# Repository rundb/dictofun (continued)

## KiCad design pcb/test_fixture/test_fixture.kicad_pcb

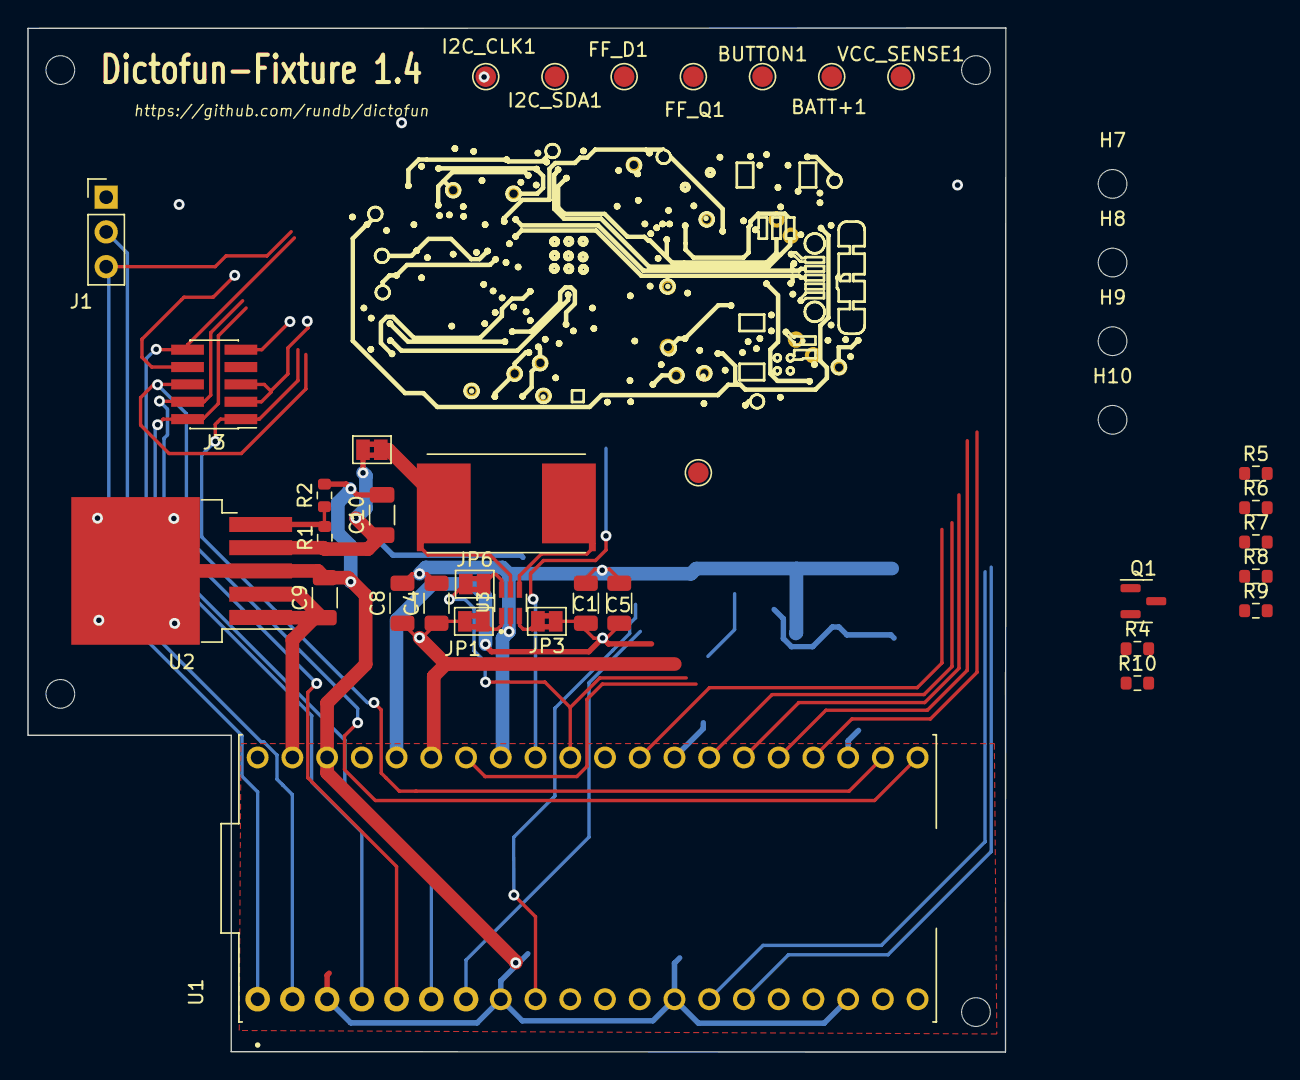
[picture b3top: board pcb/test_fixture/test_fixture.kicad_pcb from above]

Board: 2 copper layers, 71.5 x 74.9 mm, 59 parts (0 on the bottom side), 30 nets.

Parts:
BATT+1: TestPoint_Pad_D1.5mm
BUTTON1: TestPoint_Pad_D1.5mm
C1, C4: 1u; R_1206_3216Metric
C5, C8: 100n; R_1206_3216Metric
C9: 10u; R_1206_3216Metric
C10: 22u; C_1206_3216Metric
FF_CLK1: TestPoint_Pad_D1.5mm
FF_D1: TestPoint_Pad_D1.5mm
FF_Q1: TestPoint_Pad_D1.5mm
H3, H4, H5, H6: Outer PCB Mount; MountingHole_2.1mm
H7, H8, H9, H10: Stand Mount; MountingHole_2.1mm
I2C_CLK1, I2C_SDA1: TestPoint_Pad_D1.5mm
J1: UART; PinHeader_1x03_P2.54mm_Vertical
J3: Conn_ARM_JTAG_SWD_10; PinHeader_2x05_P1.27mm_Vertical_SMD
JP1, JP3, JP5, JP6: Jumper_2_Bridged; SolderJumper-2_P1.3mm_Bridged2Bar_Pad1.0x1.5mm
POGO1, POGO2, POGO3, POGO5, POGO6, POGO7, POGO8, POGO10, POGO11, POGO12, POGO13, POGO14, POGO15, POGO16, POGO19, POGO21, POGO22: pogo; POGO
Q1: NMOS; SOT-23
R1: 415; R_0603_1608Metric
R2: 187; R_0603_1608Metric
R3: 0.04; R_Shunt_Vishay_WSR2_WSR3_KelvinConnection
R4, R5, R6: 100K; R_0603_1608Metric
R7: 200K; R_0603_1608Metric
R8: 300K; R_0603_1608Metric
R9, R10: 1K; R_0603_1608Metric
U1: SC0915; MODULE_SC0915
U2: MIC29302WU; TO-263-5_TabPin3
U3: INA186A5IDCKR; SOT65P210X110-6N
VCC_SENSE1: TestPoint_Pad_D1.5mm

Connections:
+3.3V: C1.1, C5.1, JP3.1 (A), U1.36 (3V3_OUT)
+3.3VADC: C4.1, C8.1, JP1.1 (A), U1.35 (ADC_VREF)
+5V: C9.1, U1.39 (VSYS), U2.1 (EN), U2.2 (VIN)
/BATT+: BATT+1.1, POGO13.1, POGO19.1, R3.2, U3.4
/BUTTON: BUTTON1.1, POGO7.1, Q1.3 (S), R7.1
/BUTTON_CTRL: R4.1, R9.1, R10.1
/BUTTON_DIVIDED: R7.2, R8.1, U1.7 (GP5)
/CURRENT_SENSE_OUTPUT: JP6.1 (A), U1.31 (GP26)
/FF_CLK: FF_CLK1.1, POGO10.1, U1.26 (GP20)
/FF_D: FF_D1.1, POGO8.1, U1.27 (GP21)
/FF_Q: FF_Q1.1, POGO15.1, U1.29 (GP22)
/I2C_CLK: I2C_CLK1.1, POGO11.1, U1.24 (GP18)
/I2C_DATA: I2C_SDA1.1, POGO12.1, U1.25 (GP19)
/P1.9V: POGO16.1, VCC_SENSE1.1
/SENSE_VCC: R5.2, R6.1
/SWDCLK: J3.4 (SWDCLK/TCK), POGO21.1, U1.5 (GP3)
/SWDIO: J3.2 (SWDIO/TMS), POGO22.1, U1.6 (GP4)
/UART_RX: J1.3, POGO1.1, U1.1 (GP0)
/UART_TX: J1.2, POGO5.1, U1.2 (GP1)
/VTREF: J3.1 (VTref), POGO2.1, U1.22 (GP17)
GND: C9.2, C10.2, J1.1, J3.3 (GND), J3.5 (GND), POGO3.1, POGO6.1, POGO14.1, R2.2, R4.2, R6.2, R8.2, U1.3 (GND), U1.8 (GND), U1.13 (GND), U1.18 (GND), U1.23 (GND), U1.28 (GND), U1.38 (GND), U2.3 (GND)
GNDA: C1.2, C4.2, C5.2, C8.2, U1.33 (AGND), U3.2
unnamed: JP1.2 (B), U3.1
unnamed: JP3.2 (B), U3.3
unnamed: JP5.2 (B), R3.1, U3.5
unnamed: JP6.2 (B), U3.6
unnamed: Q1.2 (G), R10.2
unnamed: R9.2, U1.9 (GP6)
unnamed: R1.2, R2.1, U2.5 (ADJ)
VDD: C10.1, JP5.1 (A), Q1.1 (D), R1.1, U2.4 (VOUT)

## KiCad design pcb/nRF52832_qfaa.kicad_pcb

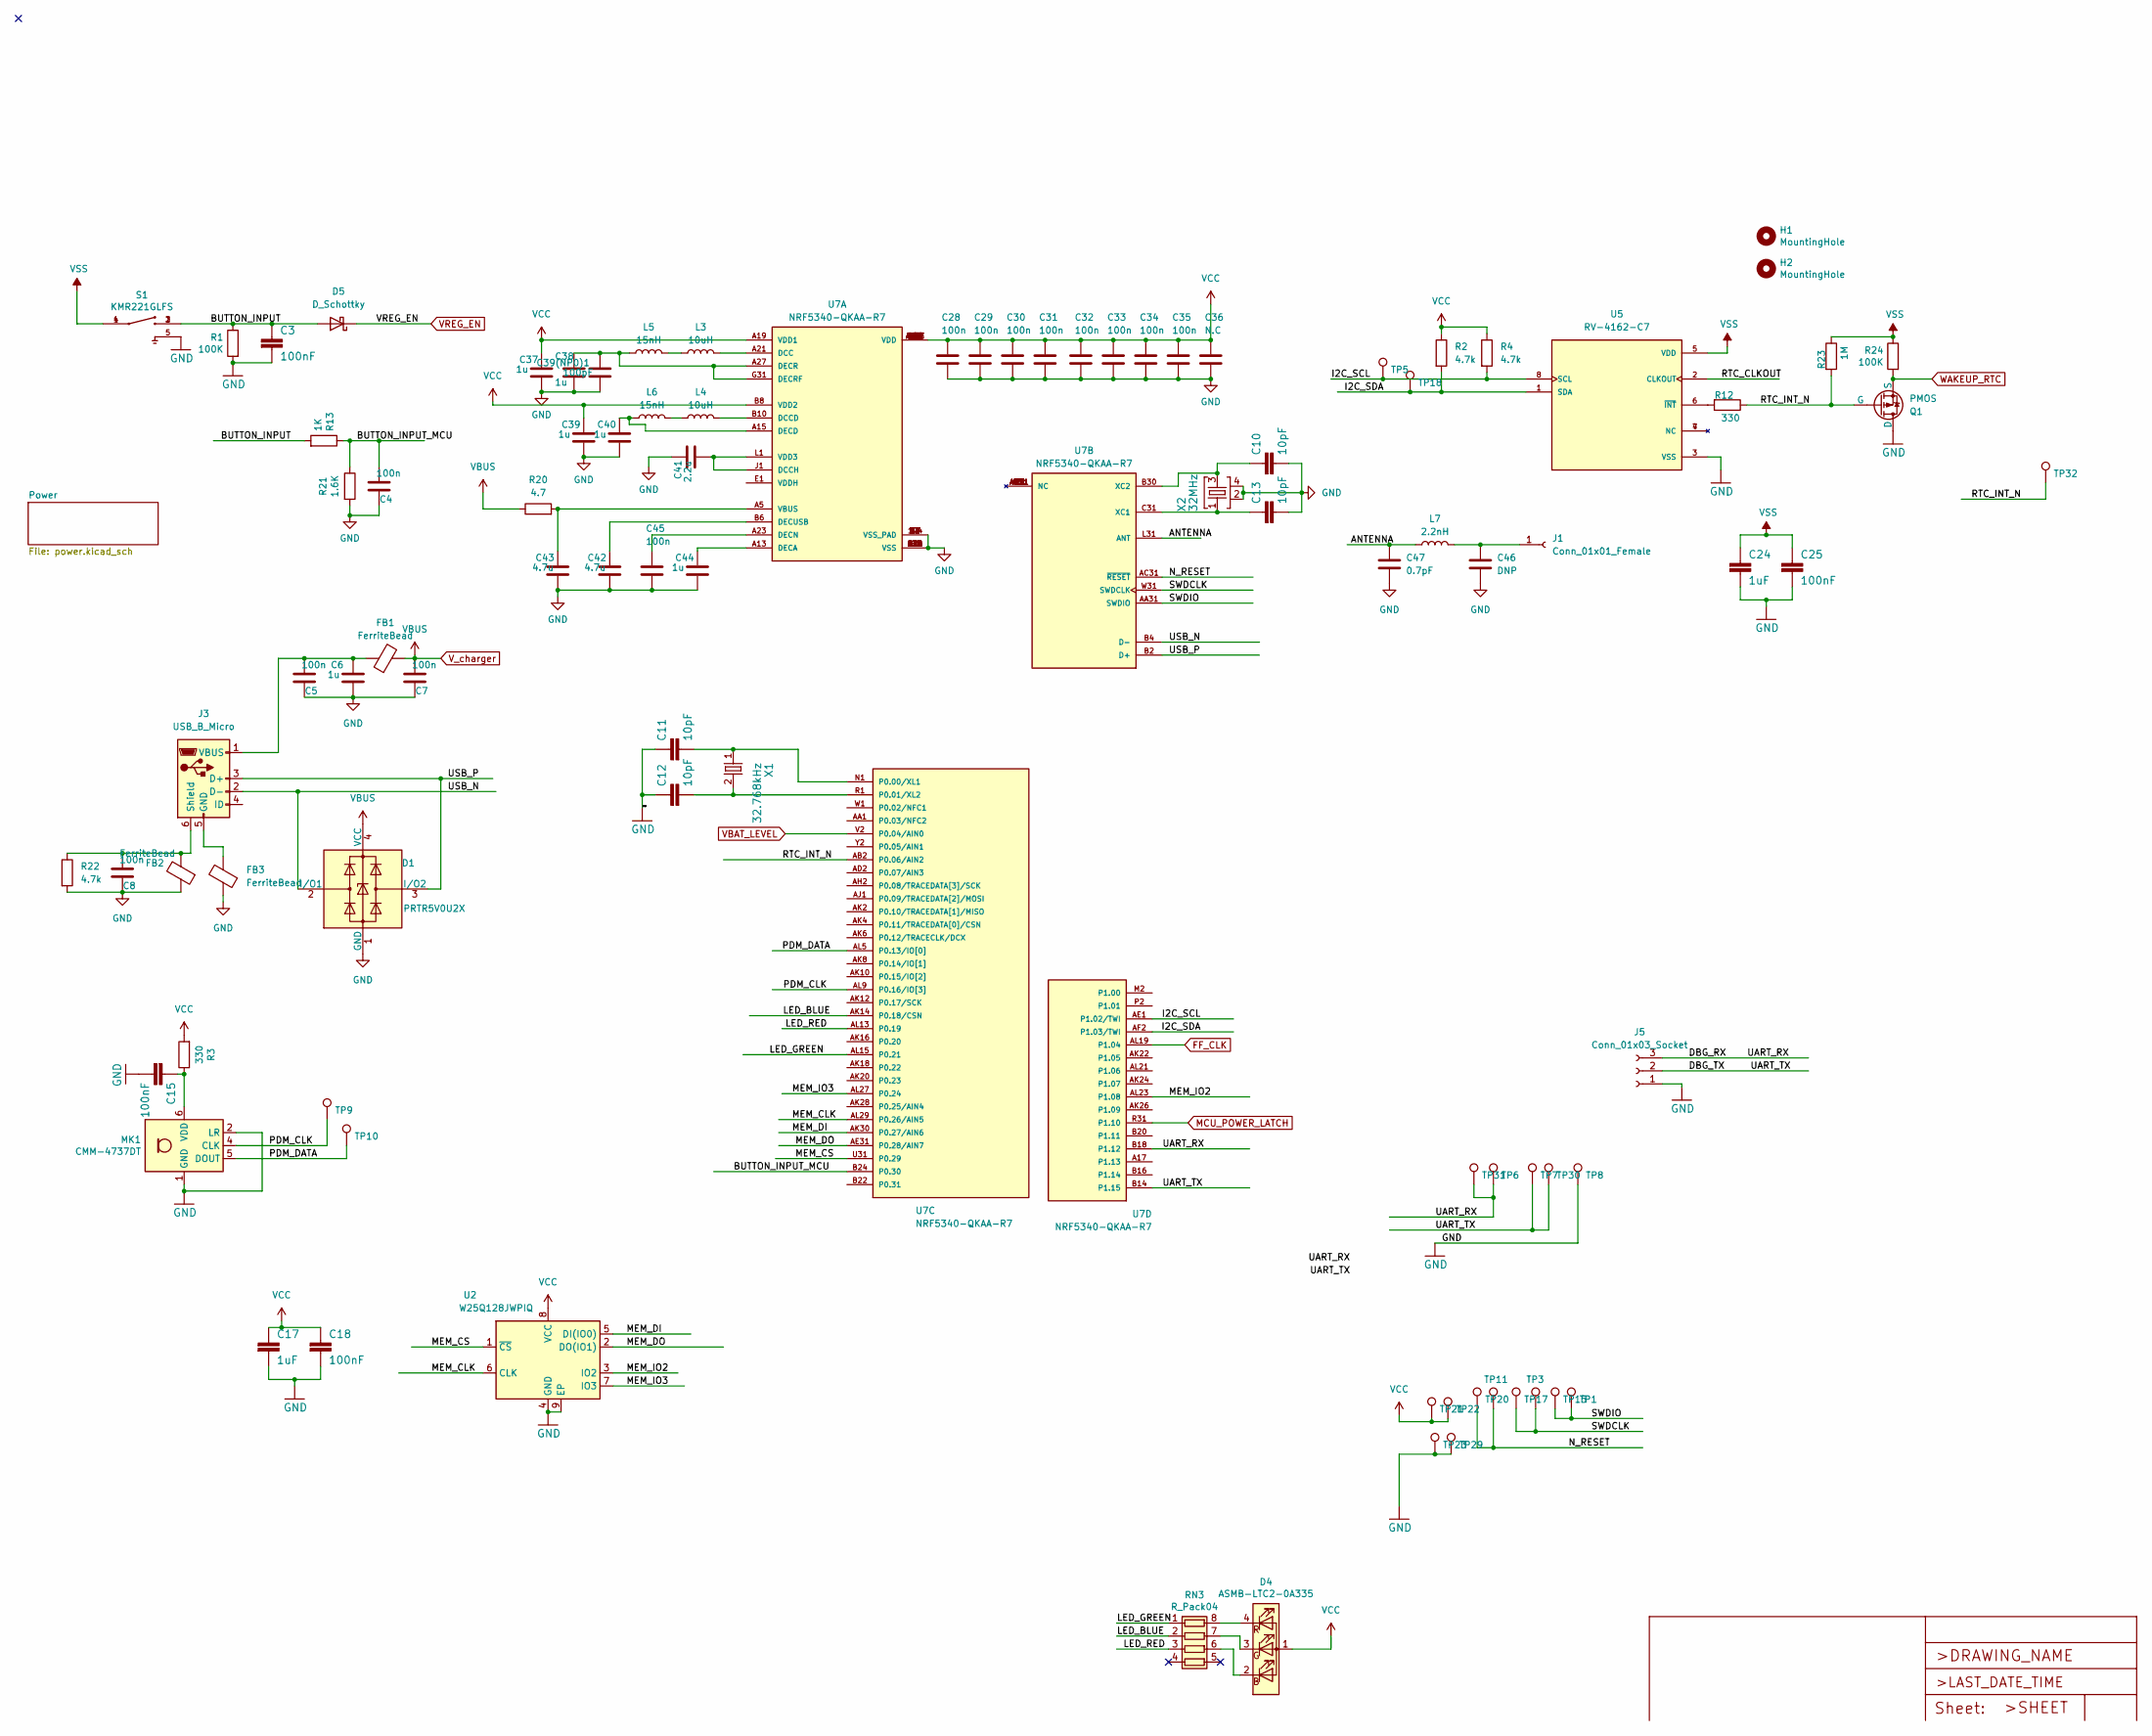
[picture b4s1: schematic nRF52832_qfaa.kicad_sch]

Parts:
C3, C15, C18, C25: 100nF; C_0402_1005Metric; LCSC C1525
C4, C5, C7, C8, C28, C29, C30, C31, C32, C33, C34, C35, C45: 100n; C_0201_0603Metric; LCSC C5142565
C6, C37, C38, C39, C40, C44: 1u; C_0402_1005Metric; LCSC C77007
C10, C13: 10pF; C_0402_1005Metric; LCSC C32949
C11, C12: 10pF; C_0201_0603Metric
C17, C24: 1uF; C_0402_1005Metric; LCSC C52923
C36: N.C; C_0201_0603Metric
C39(NP0)1: 100pF; C_0201_0603Metric
C41: 2.2u; C_0603_1608Metric; LCSC C77183
C42: 4.7u; C_0603_1608Metric; LCSC C2961288
C43: 4.7u; C_0603_1608Metric; LCSC C108342
C46: DNP; C_0201_0603Metric
C47: 0.7pF; C_0201_0603Metric
D1: PRTR5V0U2X; SOT-143; LCSC C2827688
D4: ASMB-LTC2-0A335; LED_Cree-PLCC4_2x2mm_CW
D5: D_Schottky; D_SOD-123F; LCSC C223608
FB1, FB2, FB3: FerriteBead; L_0402_1005Metric; LCSC C19136
H1, H2: MountingHole; MountingHole_1mm
J1: Conn_01x01_Female; PinHeader_1x01_P1.00mm_Vertical
J3: USB_B_Micro; USB_Micro-B_Molex-105017-0001
J5: Conn_01x03_Socket; JST_SM03B-SRSS-TB_LF__SN_
L3, L4: 10uH; L_0603_1608Metric; LCSC C5339208
L5, L6: 15nH; L_0201_0603Metric; LCSC C1332892
L7: 2.2nH; L_0201_0603Metric
MK1: CMM-4737DT; ST_HLGA-6_3.76x4.72mm_P1.65mm
Q1: PMOS; SOT-23; LCSC C332106
R1, R24: 100K; R_0402_1005Metric; LCSC C25741
R2, R4, R22: 4.7k; R_0402_1005Metric; LCSC C25900
R3, R12: 330; R_0402_1005Metric; LCSC C25104
R13: 1K; R_0402_1005Metric; LCSC C11702
R20: 4.7; R_0201_0603Metric; LCSC C166070
R21: 1.6K; R_0402_1005Metric; LCSC C25867
R23: 1M; R_0402_1005Metric; LCSC C226699
RN3: R_Pack04; R_Array_Convex_4x0402; LCSC C25726
S1: KMR221GLFS; SW_KMR221GLFS; LCSC C72443
TP1, TP3, TP5, TP6, TP7, TP8, TP9, TP10, TP11, TP15, TP17, TP18, TP20, TP21, TP22, TP23, TP29, TP30, TP31, TP32: TestPoint; TestPoint_Pad_D1.0mm
U2: W25Q128JWPIQ; WSON-8-1EP_6x5mm_P1.27mm_EP3.4x4.3mm; LCSC C2689660
U5: RV-4162-C7; IC_RV-4162-C7; PARTREV 5.1/09.2020
U7: NRF5340-QKAA-R7; XCVR_NRF5340-QKAA-R7; PARTREV 1.0
X1: 32.768kHz; Crystal_SMD_MicroCrystal_CM9V-T1A-2Pin_1.6x1.0mm
X2: 32MHz; BT-XTAL_2016_N

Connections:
/ANTENNA: C47.1, L7.1, U7.L31 (ANT)
/BUTTON_INPUT: C3.1, D5.2 (A), R1.1, R13.2, S1.2, S1.3
/BUTTON_INPUT_MCU: C4.1, R13.1, R21.1, U7.B24 (P0.30)
/DBG_RX: J5.3, TP6.1, TP31.1, U7.B18 (P1.12)
/DBG_TX: J5.2, TP7.1, TP30.1, U7.B14 (P1.15)
/I2C_SCL: R4.2, TP5.1, U5.8 (SCL), U7.AE1 (P1.02/TWI)
/I2C_SDA: R2.2, TP18.1, U5.1 (SDA), U7.AF2 (P1.03/TWI)
/LED_BLUE: RN3.2 (R2.1), U7.AK14 (P0.18/CSN)
/LED_GREEN: RN3.1 (R1.1), U7.AL15 (P0.21)
/LED_RED: RN3.3 (R3.1), U7.AL13 (P0.19)
/MEM_CLK: U2.6 (CLK), U7.AL29 (P0.26/AIN5)
/MEM_CS: U2.1 (~CS), U7.U31 (P0.29)
/MEM_DI: U2.5 (DI(IO0)), U7.AK30 (P0.27/AIN6)
/MEM_DO: U2.2 (DO(IO1)), U7.AE31 (P0.28/AIN7)
/MEM_IO2: U2.3 (IO2), U7.AL23 (P1.08)
/MEM_IO3: U2.7 (IO3), U7.AL27 (P0.24)
/N_RESET: TP11.1, TP20.1, U7.AC31 (~RESET)
/PDM_CLK: MK1.4 (CLK), TP9.1, U7.AL9 (P0.16/IO[3])
/PDM_DATA: MK1.5 (DOUT), TP10.1, U7.AL5 (P0.13/IO[0])
/RTC_CLKOUT: U5.2 (CLKOUT)
/RTC_INT_N: Q1.2 (G), R12.1, R23.2, TP32.1, U7.AB2 (P0.06/AIN2)
/SWDCLK: TP3.1, TP17.1, U7.W31 (SWDCLK)
/SWDIO: TP1.1, TP15.1, U7.AA31 (SWDIO)
/USB_N: D1.2 (I/O1), J3.2 (D-), U7.B4 (D-)
/USB_P: D1.3 (I/O2), J3.3 (D+), U7.B2 (D+)
FF_CLK: U7.AL19 (P1.04); also elsewhere on the board
GND: C3.2, C4.2, C5.2, C6.2, C7.2, C8.2, C10.2, C11.1, C12.1, C13.2, C15.2, C17.2, C18.2, C24.2, C25.2, C28.2, C29.2, C30.2, C31.2, C32.2, C33.2, C34.2, C35.2, C36.2, C37.2, C38.2, C39.2, C39(NP0)1.2, C40.2, C41.1, C42.2, C43.2, C44.2, C45.2, C46.2, C47.2, D1.1 (GND), FB2.1, FB3.1, J5.1, MK1.1 (GND), MK1.2 (LR), MK1.3 (GND), Q1.1 (D), R1.2, R21.2, R22.2, S1.5, TP8.1, TP23.1, TP29.1, U2.4 (GND), U2.9 (EP), U5.3 (VSS), U7.35 (VSS_PAD), U7.36 (VSS_PAD), U7.37 (VSS_PAD), U7.38 (VSS_PAD), U7.39 (VSS_PAD), U7.40 (VSS_PAD), U7.41 (VSS_PAD), U7.43 (VSS_PAD), U7.44 (VSS_PAD), U7.45 (VSS_PAD), U7.46 (VSS_PAD), U7.47 (VSS_PAD), U7.48 (VSS_PAD), U7.49 (VSS_PAD), U7.50 (VSS_PAD), U7.51 (VSS_PAD), U7.104 (VSS_PAD), U7.A25 (VSS), U7.B12 (VSS), U7.B26 (VSS), U7.G1 (VSS), U7.H2 (VSS), U7.J31 (VSS), X2.2, X2.4; also elsewhere on the board
MCU_POWER_LATCH: U7.R31 (P1.10); also elsewhere on the board
unnamed: D4.2 (BK), RN3.6 (R3.2)
unnamed: D4.3 (GK), RN3.7 (R2.2)
unnamed: D4.4 (RK), RN3.8 (R1.2)
unnamed: C46.1, J1.1, L7.2
unnamed: FB3.2, J3.5 (GND)
unnamed: C8.1, FB2.2, J3.6 (Shield), R22.1
unnamed: C5.1, C6.1, FB1.1, J3.1 (VBUS)
unnamed: L3.1, L5.2
unnamed: L4.1, L6.2
unnamed: C15.1, MK1.6 (VDD), R3.1
unnamed: R12.2, U5.6 (~INT)
unnamed: L3.2, U7.A21 (DCC)
unnamed: L4.2, U7.B10 (DCCD)
unnamed: C41.2, U7.J1 (DCCH), U7.L1 (VDD3)
unnamed: C44.1, U7.A13 (DECA)
unnamed: C40.1, L6.1, U7.A15 (DECD)
unnamed: C45.1, U7.A23 (DECN)
unnamed: C38.1, C39(NP0)1.1, L5.1, U7.A27 (DECR), U7.G31 (DECRF)
unnamed: C42.1, U7.B6 (DECUSB)
unnamed: C43.1, R20.2, U7.A5 (VBUS)
unnamed: C13.1, U7.C31 (XC1), X2.1
unnamed: C10.1, U7.B30 (XC2), X2.3
unnamed: C11.2, U7.N1 (P0.00/XL1), X1.1
unnamed: C12.2, U7.R1 (P0.01/XL2), X1.2
VBAT_LEVEL: U7.V2 (P0.04/AIN0); also elsewhere on the board
VCC: C17.1, C18.1, C28.1, C29.1, C30.1, C31.1, C32.1, C33.1, C34.1, C35.1, C36.1, C37.1, C39.1, D4.1 (A), R2.1, R3.2, R4.1, TP21.1, TP22.1, U2.8 (VCC), U7.A19 (VDD1), U7.AC1 (VDD), U7.AG1 (VDD), U7.AJ31 (VDD), U7.AL3 (VDD), U7.AL7 (VDD), U7.AL11 (VDD), U7.AL17 (VDD), U7.AL25 (VDD), U7.B8 (VDD2), U7.B28 (VDD), U7.C1 (VDD), U7.E31 (VDD), U7.N31 (VDD), U7.U1 (VDD); also elsewhere on the board
VREG_EN: D5.1 (K), Q1.3 (S), R24.2; also elsewhere on the board
VSS: C24.1, C25.1, R23.1, R24.1, S1.1, S1.4, U5.5 (VDD); also elsewhere on the board
V_charger: C7.1, D1.4 (VCC), FB1.2, R20.1; also elsewhere on the board

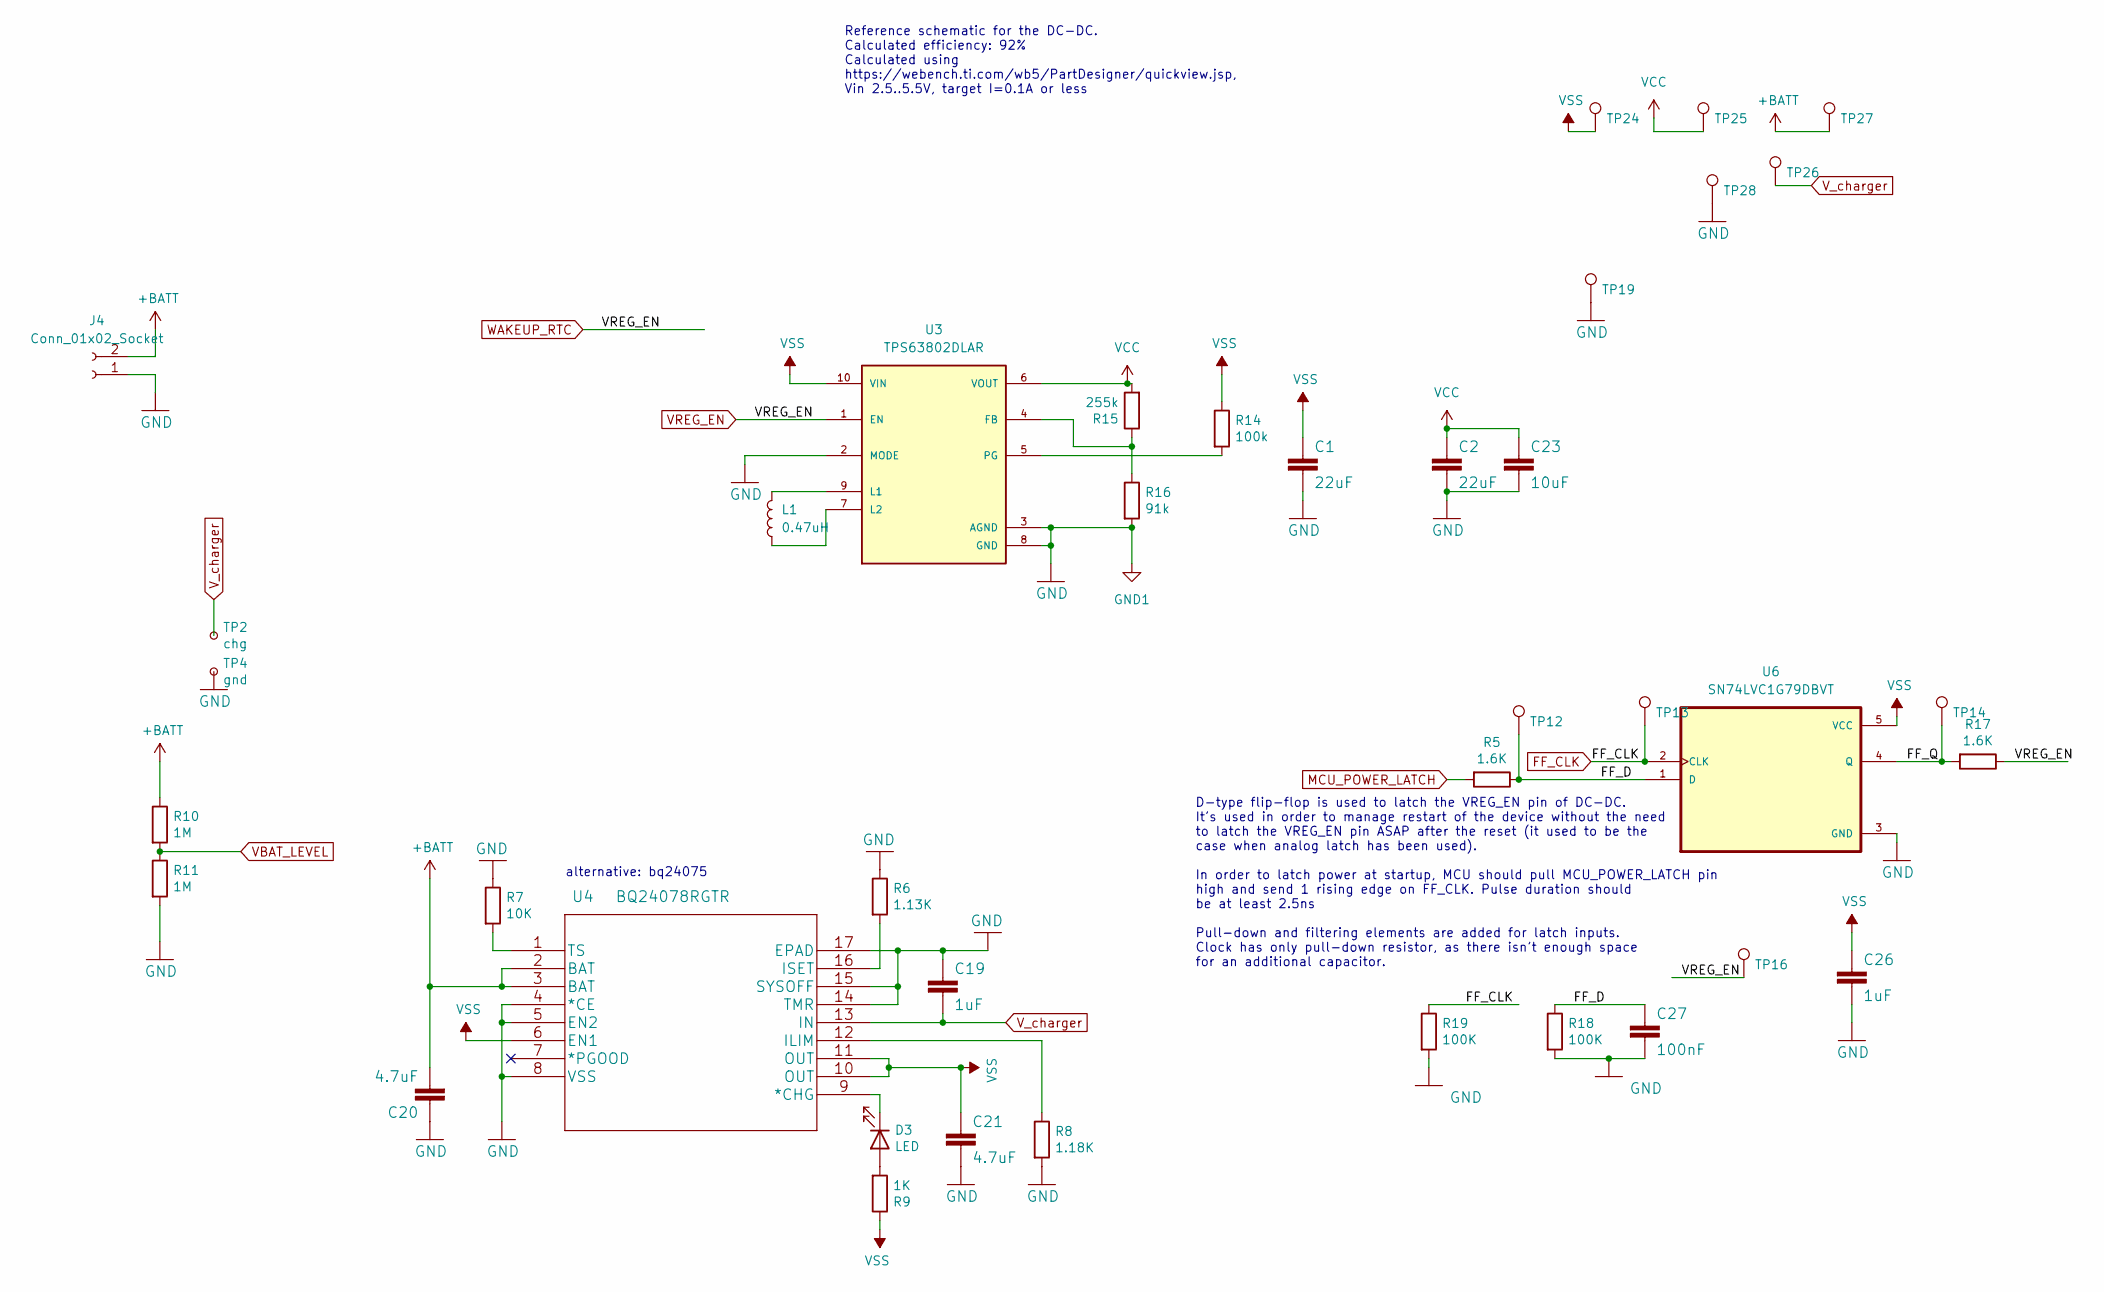
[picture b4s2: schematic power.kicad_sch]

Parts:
C1, C2: 22uF; C_0603_1608Metric; LCSC C109447
C19, C26: 1uF; C_0402_1005Metric; LCSC C52923
C20, C21: 4.7uF; C_0402_1005Metric; LCSC C23733
C23: 10uF; C_0402_1005Metric; LCSC C15525
C27: 100nF; C_0402_1005Metric; LCSC C1525
D3: LED; LED_0603_1608Metric; LCSC C131282
J4: Conn_01x02_Socket; SM02B-SRSS-TB_LF__SN_
L1: 0.47uH; L_1008_2520Metric; PartN LQM2HPNR47MG0L; LCSC C1333867
R5, R17: 1.6K; R_0402_1005Metric; LCSC C25867
R6: 1.13K; R_0402_1005Metric; LCSC C67014
R7: 10K; R_0402_1005Metric; LCSC C25744
R8: 1.18K; R_0402_1005Metric; LCSC C270651
R9: 1K; R_0402_1005Metric; LCSC C11702
R10, R11: 1M; R_0402_1005Metric; LCSC C226699
R14: 100k; R_0402_1005Metric; LCSC C25741
R15: 255k; R_0603_1608Metric; LCSC C728604
R16: 91k; R_0603_1608Metric; LCSC C227535
R18, R19: 100K; R_0402_1005Metric; LCSC C25741
TP2: chg; TestPoint_Pad_D1.0mm
TP4: gnd; TestPoint_Pad_D1.0mm
TP12, TP13, TP14, TP16, TP19, TP24, TP25, TP26, TP27, TP28: TestPoint; TestPoint_Pad_D1.0mm
U3: TPS63802DLAR; VREG_TPS63802DLAR; PARTREV B; LCSC C2845237
U4: BQ24078RGTR; VQFN-16-1EP_3x3mm_P0.5mm_EP1.45x1.45mm_ThermalVias; LCSC C15464
U6: SN74LVC1G79DBVT; SOT-23-5; LCSC C42878

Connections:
+BATT: C20.2, J4.2, R10.1, TP27.1, U4.2 (BAT), U4.3 (BAT)
/Power/FF_D: C27.1, R5.1, R18.1, TP12.1, U6.1 (D)
/Power/FF_Q: R17.2, TP14.1, U6.4 (Q)
FF_CLK: R19.1, TP13.1, U6.2 (CLK); also elsewhere on the board
GND: C1.2, C2.2, C19.1, C20.1, C21.2, C23.2, C26.2, C27.2, J4.1, R6.1, R7.1, R8.2, R11.2, R16.2, R18.2, R19.2, TP4.1, TP19.1, TP28.1, U3.2 (MODE), U3.3 (AGND), U3.8 (GND), U4.4 (*CE), U4.5 (EN2), U4.8 (VSS), U4.14 (TMR), U4.15 (SYSOFF), U4.17 (EPAD), U6.3 (GND); also elsewhere on the board
MCU_POWER_LATCH: R5.2; also elsewhere on the board
unnamed: D3.2 (A), R9.2
unnamed: D3.1 (K), U4.9 (*CHG)
unnamed: R15.1, R16.1, U3.4 (FB)
unnamed: L1.2, U3.9 (L1)
unnamed: L1.1, U3.7 (L2)
unnamed: R14.2, U3.5 (PG)
unnamed: R8.1, U4.12 (ILIM)
unnamed: R6.2, U4.16 (ISET)
unnamed: R7.2, U4.1 (TS)
VBAT_LEVEL: R10.2, R11.1; also elsewhere on the board
VCC: C2.1, C23.1, R15.2, TP25.1, U3.6 (VOUT); also elsewhere on the board
VREG_EN: R17.1, TP16.1, U3.1 (EN); also elsewhere on the board
VSS: C1.1, C21.1, C26.1, R9.1, R14.1, TP24.1, U3.10 (VIN), U4.6 (EN1), U4.10 (OUT), U4.11 (OUT), U6.5 (VCC); also elsewhere on the board
V_charger: C19.2, TP2.1, TP26.1, U4.13 (IN); also elsewhere on the board

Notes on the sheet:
alternative: bq24075
D-type flip-flop is used to latch the VREG_EN pin of DC-DC. It's used in order to manage restart of the device without the need to latch the VREG_EN pin ASAP after the reset (it used to be the case when analog latch has been used). In order to latch power at startup, MCU should pull MCU_POWER_LATCH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
Reference schematic for the DC-DC. Calculated efficiency: 92% Calculated using https://webench.ti.com/wb5/PartDesigner/quickview.jsp, Vin 2.5..5.5V, target I=0.1A or less

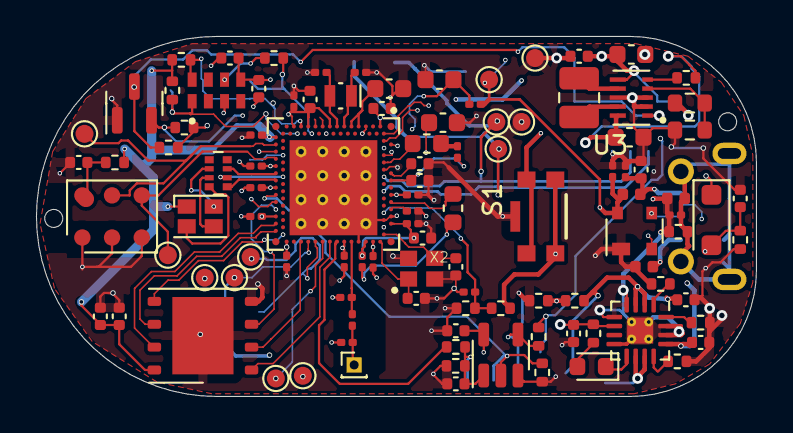
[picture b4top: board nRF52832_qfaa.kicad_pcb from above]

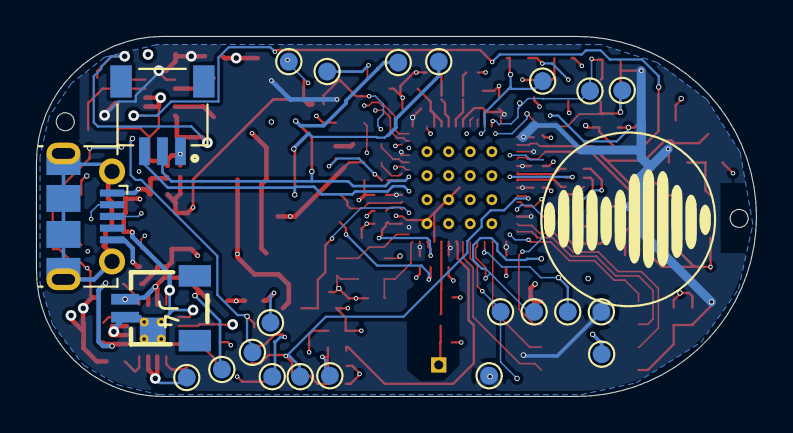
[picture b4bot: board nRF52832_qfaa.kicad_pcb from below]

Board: 4 copper layers, 40.0 x 20.0 mm, 131 parts (23 on the bottom side), 68 nets.

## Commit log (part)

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2023-01-07 implemented a primitive raw audio data sink
2023-01-08 fixes upon review
2023-01-08 [nordic] implement PDM microphone (#77)
    - implementation of PDM microphone using Nordic PDM driver
    - implementation of a data sync (targeting at integration tests)
2023-01-08 added littlefs as a third party submodule
2023-01-08 lfs: added basis for lfs sim api
2023-01-08 got rid of std::cout usage
2023-01-08 added checks of FS behavior into the test
2023-01-09 fixed target compilation error
2023-01-09 saving a compiling state of target build
2023-01-09 added memtest cli command
2023-01-09 cli infra is ready. time for the tests
2023-01-09 added memtest 2 + fixed bug in SPI flash driver implementation
2023-01-09 added submodule checkout step
2023-01-09 another attempt to fix actions
2023-01-09 fixed UT compilation issue due to different G++ versions
2023-01-10 [fw] introduce storage infrastructure (#78)
    - integrate LittleFS
    - change Spi Flash driver to use abstract interface (also implementing a setup for unit tests)
    - change SPI Flash to use synchronous access API
    - fix bug in SPI Flash driver (erase command has never been launched due to a wrong opcode)
    - implement all tasks- and cli- infrastructure for storage subsystem
2023-01-10 cleanup tasks dependencies
2023-01-10 start adding ble elements
2023-01-11 added all minimally necessary functions for BLE launch, debugging now
2023-01-11 few line ending corrections + some error handling for ble
2023-01-12 added LED control
2023-01-12 few more fixes
2023-01-12 [bugfix] fix SPI driver issue with the stack
2023-01-12 [nordic] uncomment test
2023-01-13 [test] added tests launcher for manual testing
2023-01-16 [test] adding test infrastructure for integration level tests
2023-01-23 kick off development of fts with newer requirements
2023-01-31 [ble] added control point actions, tested using nrfconnect
2023-02-01 managed to launch file list notification update
2023-02-02 implemented few corrections
2023-02-02 [ble fts] implemented file info sending
2023-02-03 fixed error with json + runtime error with unimplemented opener and getter
2023-02-03 finalized FTS data transfer function
2023-02-03 [ble fts] implement FTS data transfer (#86)
2023-02-03 added and tested FS status char behavior
2023-02-03 [ble fts] add FS status char (#87)
    * provide description in the specification
    * add implementation of FS status char and related infrastructure
    * add test in python for this characteristics check
2023-02-03 fix one test
2023-02-04 [test] refactor BLE tests subsystem to a reliable connection behavior
2023-02-04 added relevant methods to FTS python module, few more needed
2023-02-06 added tests of file info getter
2023-02-06 finalized tests for BLE FTS
2023-02-06 extended comments
2023-02-06 [test fts] refactoring BLE FTS infrasturcture (#89)
    * separated dictofun BLE control and FTS Client code
    * improve robustness of connection to the Dictofun
    * made test output less mouthful in case of correct execution of tests
2023-02-07 continue adding fs access boilerplate
2023-02-08 successfully established communication between BLE and mem
2023-02-08 fixed issue with lfs write operations
2023-02-09 cleaned up the tests and comments before pushing
2023-02-09 few cleanups + extend tasks readme with PNG drawing
2023-02-09 [fts] connect to fts
2023-02-09 [fts] connect get_file_info to fts (#91)
2023-02-10 file data transfer works, but tests fail to run simultaneously
2023-02-10 fix commented code in fts.py
2023-02-11 [fts] integrate fs stat to littlefs
2023-02-11 [nordic] refactor: move memtests to a separate entity
2023-02-14 managed to store multiple files with mocked data in the fs
2023-02-14 managed to store records
2023-02-15 [nordic] implement records storage (#96)
    * managed to store records
    * managed to download record to PC
2023-02-19 managed to stop losing data during the write process of the record
2023-02-19 fix review findings
2023-02-19 [nordic] introduce decimation + fix LittleFS losing data issues (#97)
2023-02-19 fix tests as well
2023-02-20 [audio] fix audio quality issue
2023-02-25 added an ADPCM decoder from nordic
2023-02-25 removed unneded comments and a dummy file
2023-02-25 [codec] introduce and implement ADPCM codec (#100)
    * introduce codec itself and basic testing infra for that
    * added header to record generation (now file type and parameters are contained inside the file)
    * added download throughput measurement on the python receiver side
2023-02-26 [nordic] fixed audio glitches issue
2023-02-26 [nordic] implemented shutdown
2023-03-11 [rtc] added boilerplate for RTC
2023-03-12 [rtc] found correct config for TWI enablement
2023-03-12 [rtc] implemented i2c scan and fixed all hw/config issues
2023-03-12 [rtc] add functional I2C driver base (#112)
2023-03-13 fixed issue with values readout, timing value now is being received correctly
2023-03-13 fixed space in the end of the file
2023-03-13 use RTC output to generate file name
2023-03-14 [button] added task_button
2023-03-17 [nvm] added non-volatile storage config support
2023-03-17 [nvm] added non-volatile storage config support (#116)
2023-03-17 [ci] assuring sequential execution of jobs
2023-03-18 fixed error check result error
2023-03-18 [state] refactor task state: move cli logic out of main body
2023-03-18 [state] refactor task_state (#119)
    * [state] refactor task state: move cli logic out of main body
    * [state] move power control to separate compilation unit
2023-03-18 [state] implemented record upon button press
2023-03-18 [state] implement memory ownership switch in field modes
2023-03-19 [app] introduced shutdown upon timeout in application modes
2023-03-19 [app] implemented filesystem access keepalive for power management
2023-03-19 [led] start adding boilerplate for led implementation
2023-03-19 [led] implemented LED control
2023-03-19 [led] implement LED control (#124)
    * implemented LED control
    * implemented CLI commands for testing
2023-03-19 [led] implemented application indication (#125)
2023-03-26 [ble] implement pairing and unpairing
2023-03-30 [nordic] create patch to increase SDH task stack
2023-04-25 [ci] add setup script for rpi ci (#129)
2023-04-25 [ci] add artefacts storage job (#130)
2023-04-26 [ci] split ut and target builds by directories (#131)
2023-04-27 [ci] adding download artefact action
2023-04-27 [ci] add artefacts upload/download (#132)
2023-04-27 [ci] added actual flashing of application hex (#133)
2023-05-02 [case] added models for harness v1.3
2023-06-22 fixed reset script and added env variable to ease installation script
2023-06-22 attempt to fix paths issue
2023-06-22 [doc, ci] add harness bringup documentation + fix CI (#134)
    * [harness] added instructions on building FW for the harness
    * fix CI cmake interpreter issue
2023-07-19 [ble] made write chars notifiable (#135)
2023-07-24 remove unnecessary comma change
2023-07-25 added get_next_file_list char and surrounding boilerplate
2023-08-01 fixes upon review, comments
2023-08-05 replaced some log from info to debug level
2023-08-05 started adding version generation and printout
2023-08-05 fixed paths, now version is printed out every startup
2023-08-06 removed space
2023-08-23 introduce reasonable value limitations for time elements (until proper timing logic is implemented)
2023-08-24 ble start stop seems to be working now
2023-08-24 remove irrelevant comments
2023-08-24 [ble] add BLE stop functionality (#142)
2023-08-24 [ble] added gap param update upon connection parameter change by the peer (#143)
2023-08-26 [cts] implementing OS boilerplate for date-time setup
2023-08-26 [ble cts] add BLE CTS support (#144)
2023-08-28 changed file id type and fixed all compilation issues
2023-08-28 extend several timeouts, due to inefficiency of LFS
2023-08-28 [app] reduced timeouts before the shutdown
2023-09-25 added workaround and a warning regarding the new FS issue (missing end of the files) (#149)
2023-10-02 fix nrf sdk patch for correct building
2023-10-07 [batt] implement battery measurement task
2023-10-07 drop CI back to self-hosting
2023-10-08 apply patches in the Docker CI image
2023-10-15 [batt] added periodic battery level print to console
2023-10-15 [batt] added periodic battery level print to console (#153)
2023-10-15 added RAII time profiling printout for memory operations
2023-10-15 added RAII time profiling printout for memory operations (#155)
2023-10-15 add BLE-enabling in case of FS error prior to reset
2023-10-15 added FS formatting if memory is full/files count is too high
2023-10-15 changed battery levels, added no-op reaction in case of a low battery
2023-10-16 changed battery levels, added no-op reaction in case of a low battery (#159)
    * changed battery levels, added no-op reaction in case of a low battery
2023-10-18 [ble] removed LBS service, might affect the background discovery on iOS (#160)
2023-11-01 added memory dump command into CLI
2023-11-01 getting started with new FS
2023-11-01 started implementation of myfs mount, need to perform first file write to test
2023-11-02 managed to program descriptor correctly
2023-11-04 managed to mount, create and close files properly
2023-11-04 added test with writing 2 files
2023-11-04 start replacing lfs with myfs in integration
2023-11-05 integrated data write, time to test the audio write scenarios
2023-11-05 integrated get_file_info
2023-11-05 added file data getter integration
2023-11-05 received the first file on the ios side
2023-11-05 fixed issue with fs stat call
2023-11-05 get rid of littlefs presence
2023-11-05 tidied the myfs_access api
2023-11-05 added restart, if 0-size FTS transaction was continuously repeated
2023-11-05 removed leftover buffer allocations after LFS
2023-11-05 fixed issues
2023-11-13 reduced battery measurements frequency, added printout in case of multiple FTS commands
2023-11-20 remove stack increase
2023-11-20 added erasure of flash memory at the formatting stage (#166)
2023-11-26 measures added to assure that timeouts don't interrupt the memory erasure (#167)
2023-11-26 fixed multiple issues (#168)
    - BLE timeouts upon double recording
    - file not found reporting
    - file system repair, if not closed file was found
2023-12-03 enabled watchdog (#169)
2023-12-03 regenerated public key, changed board to DF1.3
2023-12-03 enabling DFU support in main
2023-12-03 fixed issue with btld hanging in nrf_log_flusj
2023-12-03 reenabled watchdog, cleaned up documentation
2023-12-03 corrected patch line endings
2023-12-03 (hopefully) fixed line endings
2023-12-03 Activate Bootloader and DFU (#170)
2023-12-31 fixed myfs repair infinite loop issue
2024-01-13 added additional check of button state before creating a record (#171)
2024-01-13 implemented unpairing (should be moved to device information service) (#172)
2024-01-16 assured correctness of written values
2024-01-18 added edge case of a single file
2024-01-19 wiped nrf_log mentions from myfs implementation
2024-01-19 fixed bug during fs stats call
2024-02-03 added correct closure of file in out of memory case
2024-02-09 added state transitions
2024-02-09 added polling comms between state and button tasks
2024-02-10 implemented basic out-of-memory and memory corruption use-cases
2024-02-10 added timeout processing into the main execution line, timeouts need to be adjusted
2024-02-10 a few changes on handling out of memory state
2024-02-10 moved LED control to BLE as well; fixed timeouts' issue
2024-02-11 [ci] attempt to fix self-hosted runner build folder rights issue
2024-02-17 saving the changes
2024-02-23 finalizing 1.4, going for the dry run
2024-02-23 Design Freeze DF 1.4
2024-02-23 prepared the df1.4 fabrication outputs
2024-03-13 df 1.4.52840 ready for production
2024-03-24 refactoring: collect library components at one spot, separate 1.4.52840 into a separate folder
2024-03-30 v1.4.52840 harness done
2024-03-30 applied changes after placing engineering files for fixture to JLCPCB
2024-04-14 PCB v1.4 (#175)
2024-05-05 workaround for the memory corruption issue
2024-05-06 corrected comments, removed commented code
2024-06-01 fixed initial battery level value setting
2024-06-23 working on bootloader, update is not yet working reliably
